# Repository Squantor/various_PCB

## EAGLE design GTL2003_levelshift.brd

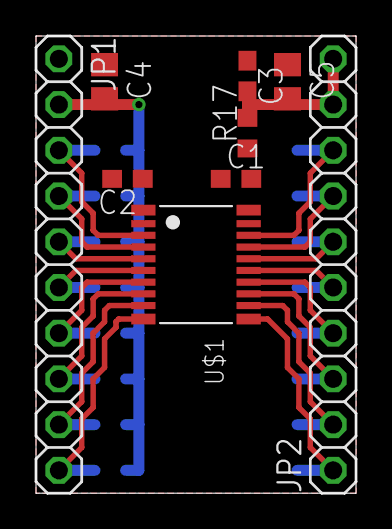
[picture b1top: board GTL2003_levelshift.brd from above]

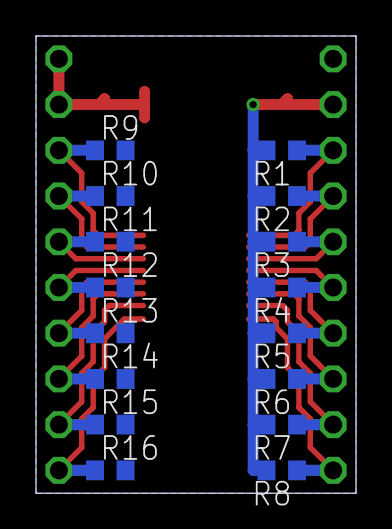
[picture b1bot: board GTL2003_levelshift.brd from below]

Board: 2 copper layers, 17.8 x 25.4 mm, 25 parts (16 on the bottom side), 20 nets.

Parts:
C1, C2, C3: 100n; C0603
C4, C5: C0805
JP1, JP2: 1X10_NORMAL_OCT
R1, R2, R3, R4, R5, R6, R7, R8, R9, R10, R11, R12, R13, R14, R15, R16: R0603
R17: 200k; R0603
U$1: GTL2003PW; SOT360

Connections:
GND: C1.1, C2.1, C3.1, C4.1, C5.1, JP1.1, U$1.1
unnamed: JP1.3, R1.1, U$1.3
unnamed: JP1.4, R2.1, U$1.4
unnamed: JP1.5, R3.1, U$1.5
unnamed: JP1.6, R4.1, U$1.6
unnamed: JP1.7, R5.1, U$1.7
unnamed: JP1.8, R6.1, U$1.8
unnamed: JP1.9, R7.1, U$1.9
unnamed: JP1.10, R8.1, U$1.10
unnamed: JP2.8, R9.1, U$1.18
unnamed: JP2.7, R10.1, U$1.17
unnamed: JP2.6, R11.1, U$1.16
unnamed: JP2.5, R12.1, U$1.15
unnamed: JP2.4, R13.1, U$1.14
unnamed: JP2.3, R14.1, U$1.13
unnamed: JP2.2, R15.1, U$1.12
unnamed: JP2.1, R16.1, U$1.11
unnamed: C1.2, R17.1, U$1.19, U$1.20
VCC: C3.2, C5.2, JP2.9, JP2.10, R9.2, R10.2, R11.2, R12.2, R13.2, R14.2, R15.2, R16.2, R17.2
VCCIO: C2.2, C4.2, JP1.2, R1.2, R2.2, R3.2, R4.2, R5.2, R6.2, R7.2, R8.2, U$1.2

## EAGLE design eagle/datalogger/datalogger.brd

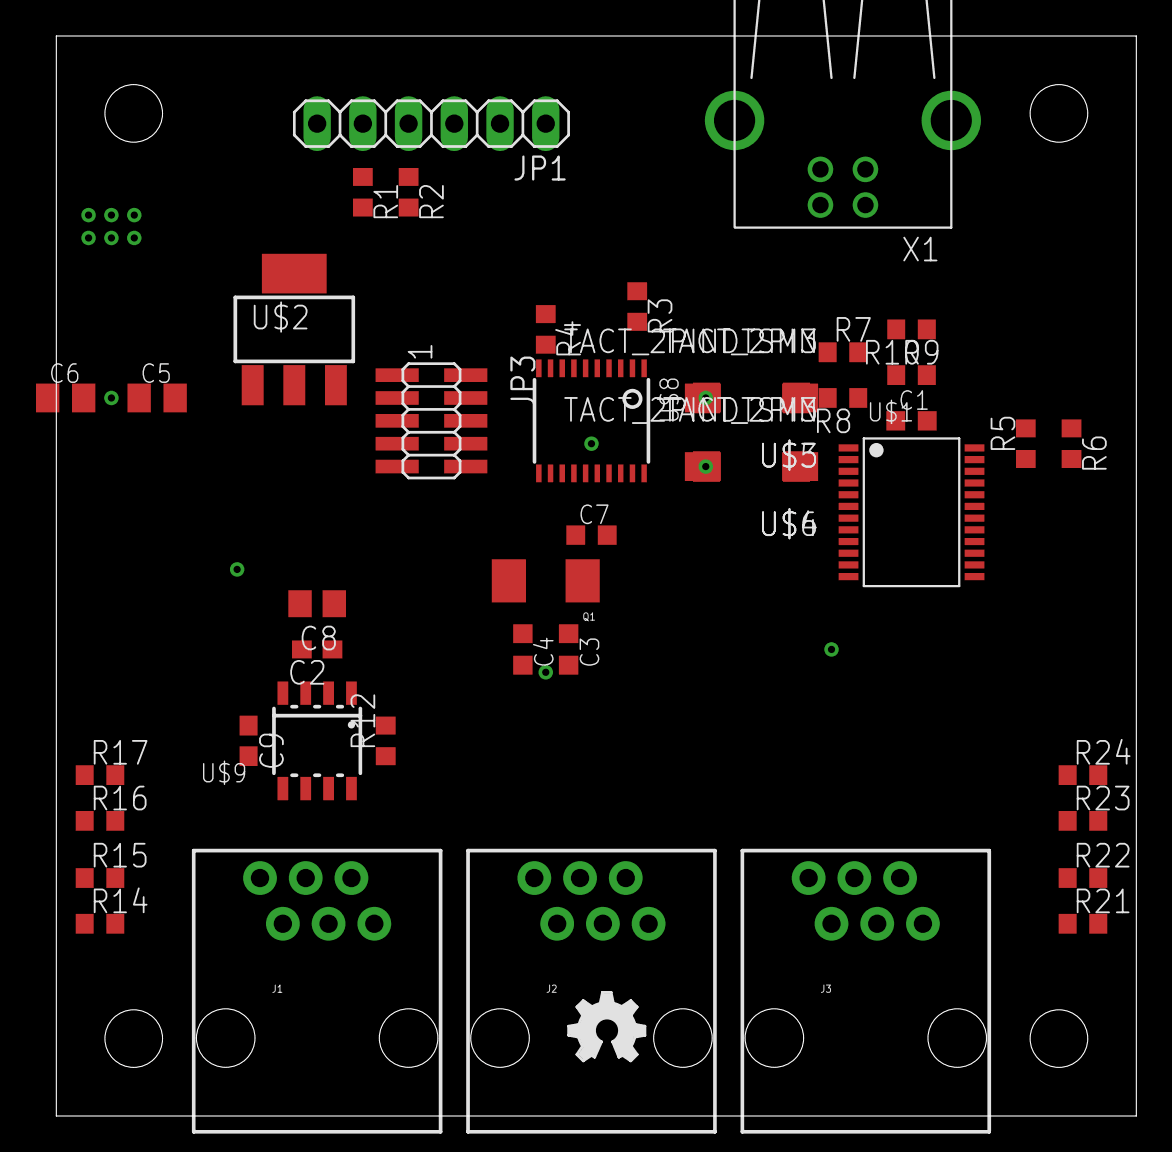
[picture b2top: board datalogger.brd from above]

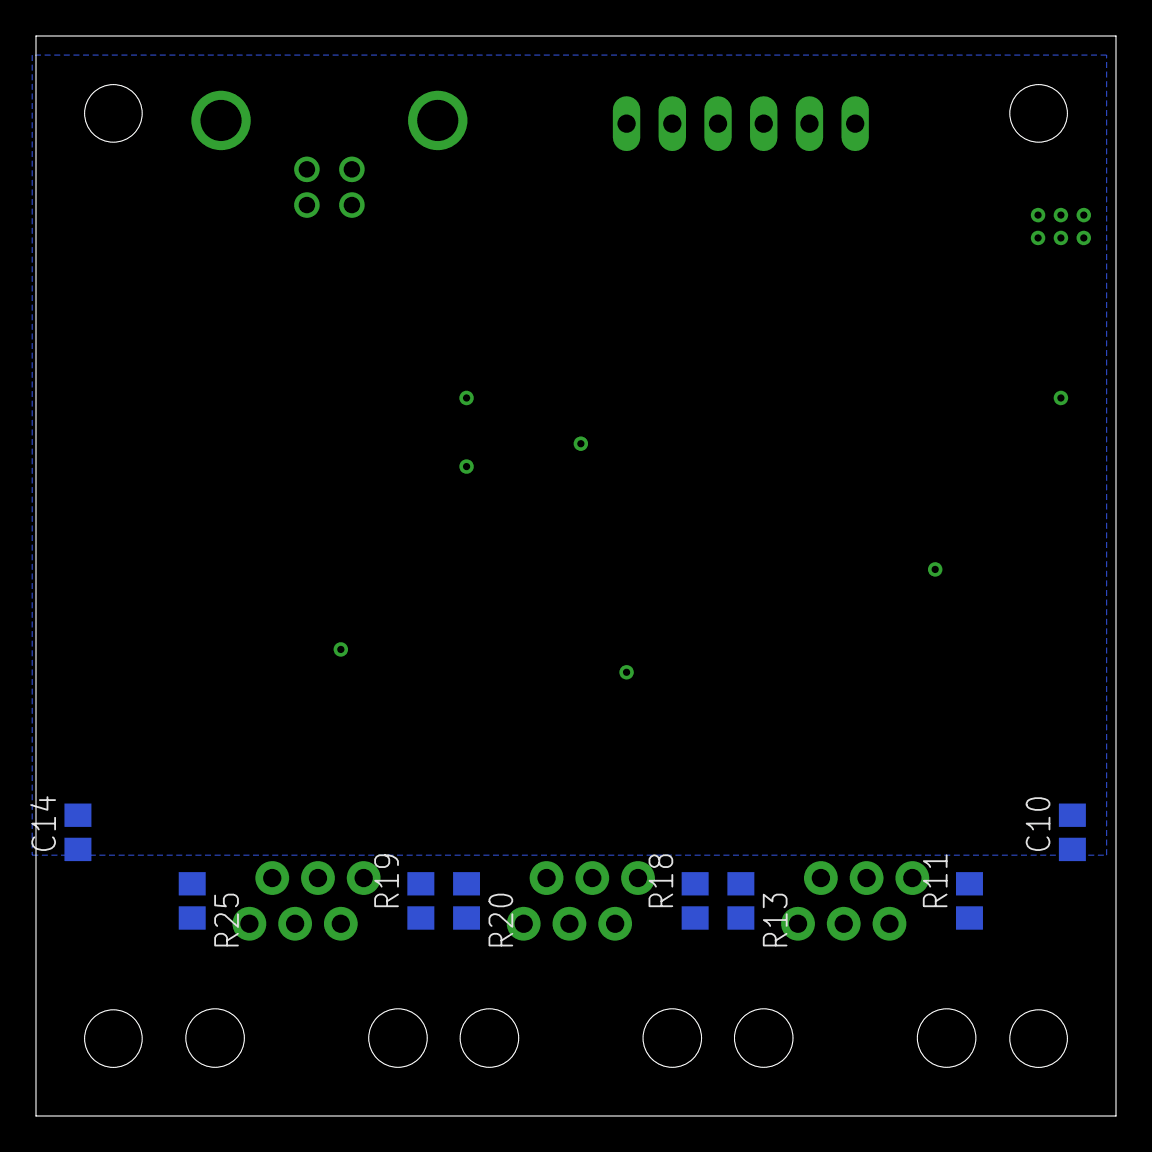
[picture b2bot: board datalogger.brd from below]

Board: 2 copper layers, 60.0 x 60.0 mm, 53 parts (8 on the bottom side), 31 nets, no tracks yet.

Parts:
C1, C7: 100n; C0603K
C2: 100n; C0603
C3, C4: 22p; C0603K
C5, C6: 1u; C0805K
C8: 2.2u; C0805
C9: DNS; C0603
C10, C14: 10n; C0805
J1, J2, J3: RJ11; RJ11-6
JP1: 1X06
JP3: JTAG; 2X05_1.27_SMD
LOGO2: OSHW_LOGO_FILLX0150-NT; OSHW_FILLX150_NOTEXT
Q1: 12MHz; CRYSTAL_5.0X3.2
R1, R2: 470; R0603
R3, R4, R5, R6, R7, R8, R9, R10: 10k; R0603
R11, R13, R18, R19, R20, R25: FB; R0805
R12: RS; R0603
R14, R15, R16, R17, R21, R22, R23, R24: 120; R0603
U$1: PCF8575; SOT340
U$2: MCP1703T-3302E/DB; SOT223
U$3, U$4: TACT_2PINDTSM3; DTSM3
U$5, U$6: TACT_2PIN; TD-85XU
U$7: FUTURLEC_PB1PB1_S; FUTURLEC_PB1_SMALL
U$8: LPC812M101JDH20; TSSOP20
U$9: PCA82C250; SOT96-1
X1: USB-B-H

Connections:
+3V3: C1.2, C5.1, C7.1, JP3.1, R3.1, R4.1, R5.2, R7.2, R9.2, U$1.24, U$2.3, U$8.15
+5V: C2.2, C6.1, C8.2, R11.2, R18.2, R19.2, U$2.1, U$9.3, X1.VBUS
CANH: J1.4, J2.4, J3.4, R15.1, R17.1, R22.1, R24.1, U$9.7
CANL: J1.3, J2.3, J3.3, R14.2, R16.2, R21.2, R23.2, U$9.6
GND: C1.1, C2.1, C3.2, C4.2, C5.2, C6.2, C7.2, C8.1, C9.1, C10.2, C14.2, JP3.3, JP3.5, JP3.9, R6.1, R8.1, R10.1, R12.2, R13.1, R20.1, R25.1, U$1.12, U$2.2, U$2.4, U$3.P$2, U$4.P$2, U$5.P$2, U$6.P$2, U$8.16, U$9.2, X1.GND
unnamed: J1.1, J1.2, R11.1
unnamed: C9.2, U$9.5
unnamed: J1.5, J1.6, R13.2
unnamed: C10.1, R14.1, R15.2, R16.1, R17.2
unnamed: R12.1, U$9.8
unnamed: J2.1, J2.2, R18.1
unnamed: J3.1, J3.2, R19.1
unnamed: J3.5, J3.6, R25.2
unnamed: J2.5, J2.6, R20.2
unnamed: C14.1, R21.1, R22.2, R23.1, R24.2
PEXP_A0: R5.1, R6.2, U$1.21
PEXP_A1: R7.1, R8.2, U$1.2
PEXP_A2: R9.1, R10.2, U$1.3
PIO0_2_SWDIO: JP3.2, U$8.7
PIO0_3_SWCLK: JP3.4, U$8.6
PIO0_5_RESET: JP3.10, R4.2, U$3.P$1, U$5.P$1, U$8.4
PIO0_8: C3.1, Q1.1, U$8.14
PIO0_9: C4.1, Q1.2, U$8.13
PIO0_10_I2C_SCL: U$1.22, U$8.9
PIO0_11_I2C_SDA: U$1.23, U$8.8
PIO0_12: R3.2, U$4.P$1, U$6.P$1, U$8.3
PIO0_13_UART_TX: R2.2, U$8.2
PIO0_16_INT: U$1.1, U$8.10
PIO0_17_UART_RX: R1.2, U$8.1
TTL_UART_RX: JP1.5, R1.1
TTL_UART_TX: JP1.4, R2.1

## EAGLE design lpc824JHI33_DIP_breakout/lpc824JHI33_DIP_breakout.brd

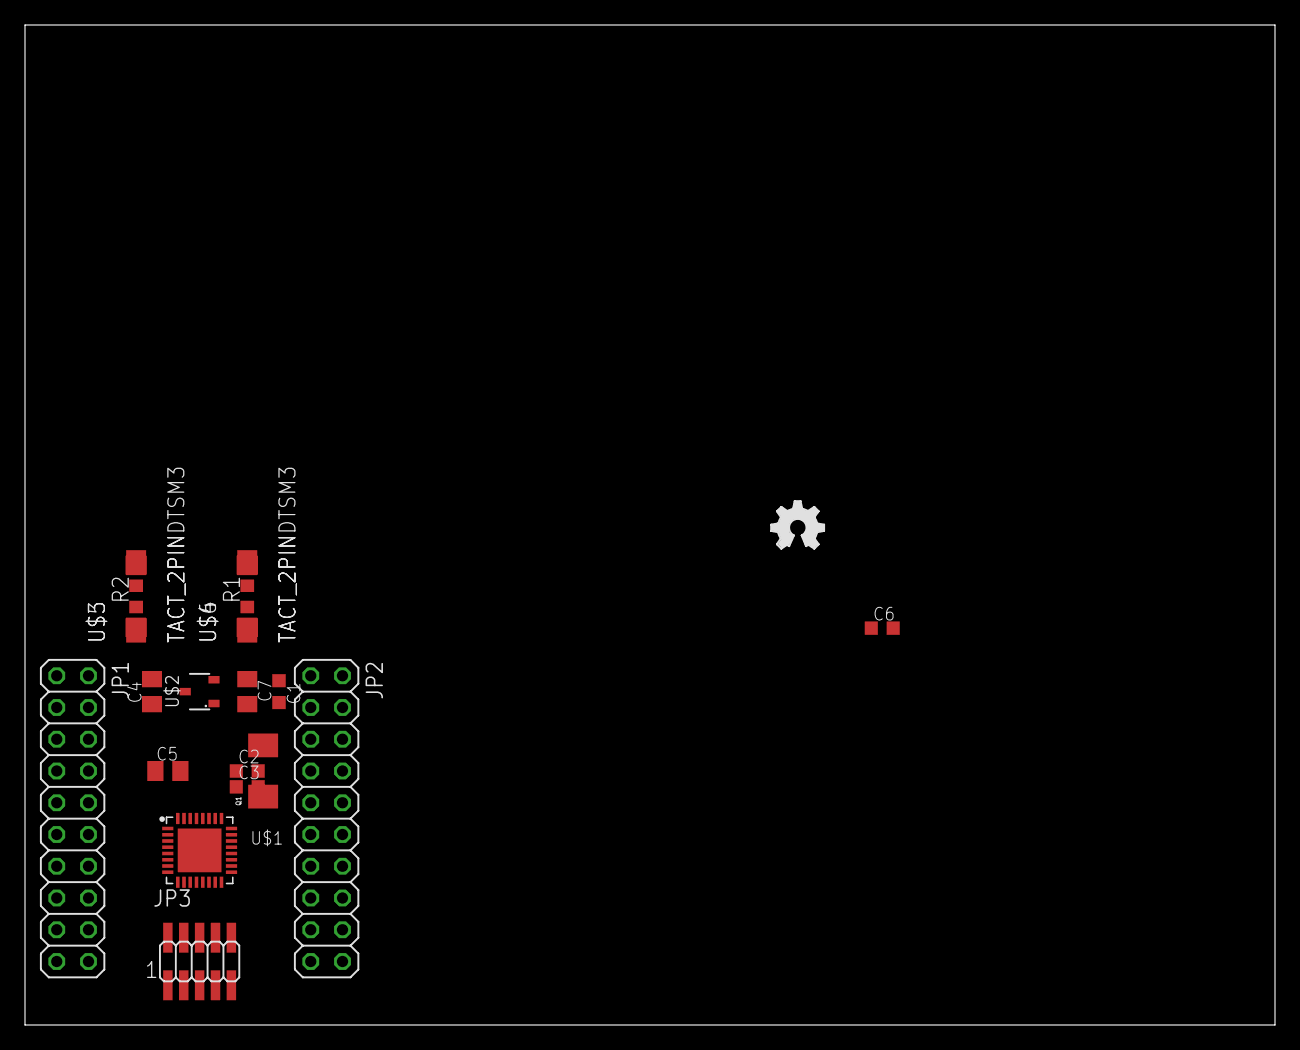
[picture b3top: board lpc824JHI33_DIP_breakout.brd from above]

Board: 2 copper layers, 100.0 x 80.0 mm, 20 parts (0 on the bottom side), 8 nets, no tracks yet.

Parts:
C1, C6: C0603K
C2, C3: 22p; C0603K
C4, C5, C7: 1u; C0805K
JP1, JP2: 2X10
JP3: JTAG; 2X05_1.27_SMD
LOGO2: OSHW_LOGO_FILLX0150-NT; OSHW_FILLX150_NOTEXT
Q1: 12MHz; CRYSTAL_5.0X3.2
R1, R2: 10k; R0603
U$1: LPC824M201JHI33; SOT617-3
U$2: TS9011; SOT23-3
U$3, U$4: TACT_2PINDTSM3; DTSM3
U$5, U$6: TACT_2PIN; TD-85XU

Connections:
DVDD: C1.1, C4.1, C7.1, JP1.1, JP1.2, JP3.1, R1.1, R2.1, U$1.19, U$2.2
DVSS: C1.2, C2.2, C3.2, C4.2, C5.2, C6.2, C7.2, JP1.3, JP1.4, JP2.3, JP2.4, JP3.3, JP3.5, JP3.9, U$1.33, U$2.1, U$3.P$2, U$4.P$2, U$5.P$2, U$6.P$2
PIO0_3: JP3.4, U$1.6
PIO0_5: JP3.10, R2.2, U$1.3, U$3.P$1, U$5.P$1
PIO0_8: C2.1, Q1.1
PIO0_9: C3.1, Q1.2
PIO0_12: R1.2, U$4.P$1, U$6.P$1
VIN: C5.1, JP2.1, JP2.2, U$2.3

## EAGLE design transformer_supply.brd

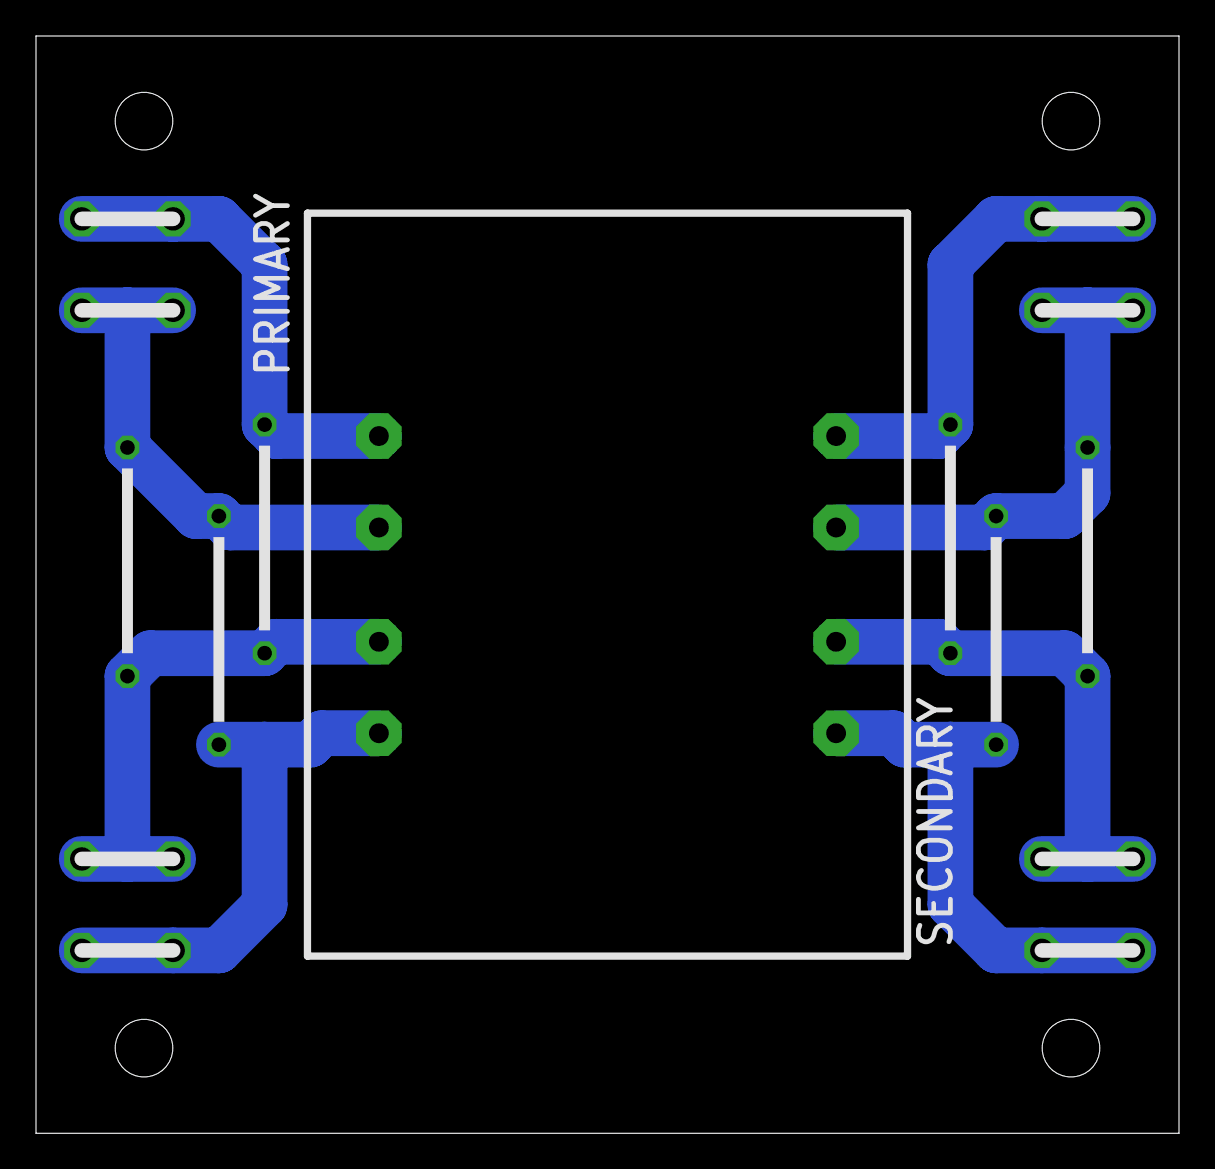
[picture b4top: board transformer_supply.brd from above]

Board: 2 copper layers, 63.5 x 61.0 mm, 15 parts (0 on the bottom side), 8 nets.

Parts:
R1, R2, R4, R5: parallel; 0309/12/BRIDGE
R3, R6: series; 0309/12/BRIDGE
U$1: VPP12-200; TRIADMAG1,5/8:1,5/16
U$2, U$3, U$4, U$5, U$6, U$7, U$8, U$9: FASTON_2PIN; FASTON_5.08

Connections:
unnamed: R1.2, R3.2, U$1.PRI1,2, U$3.1, U$3.2
unnamed: R1.1, U$1.PRI2,2, U$5.1, U$5.2
unnamed: R4.2, R6.2, U$1.SEC1,2, U$7.1, U$7.2
unnamed: R2.2, U$1.PRI1,1, U$2.1, U$2.2
unnamed: R2.1, R3.1, U$1.PRI2,1, U$4.1, U$4.2
unnamed: R4.1, U$1.SEC2,2, U$9.1, U$9.2
unnamed: R5.2, U$1.SEC1,1, U$6.1, U$6.2
unnamed: R5.1, R6.1, U$1.SEC2,1, U$8.1, U$8.2

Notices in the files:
parts and their libraries:
SparkFun-Connectors: Licensing: Creative Commons ShareAlike 4.0 International - https://creativecommons.org/licenses/by-sa/4.0
